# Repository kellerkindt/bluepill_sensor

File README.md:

# Bluepill Ethernet Sensor Extension Board

This project is about an extension board for the Bluepill (based on stm32f103) I develop in my spare time.
I use this board to monitor the temperature at various places in my house, the CO2 concentration at my desktop as well as my energy consumption.
All values are polled through the network (UDP) by munin. You can even watch some live readings [here](https://home.watzko.de).
The board is designed to be stacked on top of another expansion PCB and provides the following functionality itself:

 - an ethernet connection via W5500
 - an OneWire connector (3.3v, GND, Data)
 - an EEPROM socket (AT93C46W via DIP or SOIC)
 - temperature sensor (LM75 SOIC)
 - a (factory reset) button
 - 2x status LEDs
    - with jumpers to disconnect them from the RTC pins (PC14 & PC15)
 - 8x LEDs via on-board GPIO-I2C-Expander PCF8574 (SOIC)
 - I2C-2 connector for further frontend expansion (3.3v, GND, SDA and SCL)

 \
(Board rev 2 connected to ethernet and with an OneWire temperature sensor)

### Pinout

On the top and bottom borders the board provides the same pin-layout as the Bluepill itself.
The top row is directly connected to the Bluepill and no pin is used by the board.
Although all pins of the bottom row are used by components on the board, they are routed through nonetheless
(keep in mind that the 2x2 jumper pins can disconnect PC14 & PC15 from the board entirely - including from the bottom pins). 

## Gallery

### Animated assembly of board rev 3.1

### CO2 expansion

todo

### GPIO LED Demo

todo

#### License

<sup>
Licensed under either of <a href="LICENSE-APACHE">Apache License, Version
2.0</a> or <a href="LICENSE-MIT">MIT license</a> at your option.
</sup>

<br>

<sub>
Unless you explicitly state otherwise, any contribution intentionally submitted
for inclusion in this crate by you, as defined in the Apache-2.0 license, shall
be dual licensed as above, without any additional terms or conditions.
</sub>

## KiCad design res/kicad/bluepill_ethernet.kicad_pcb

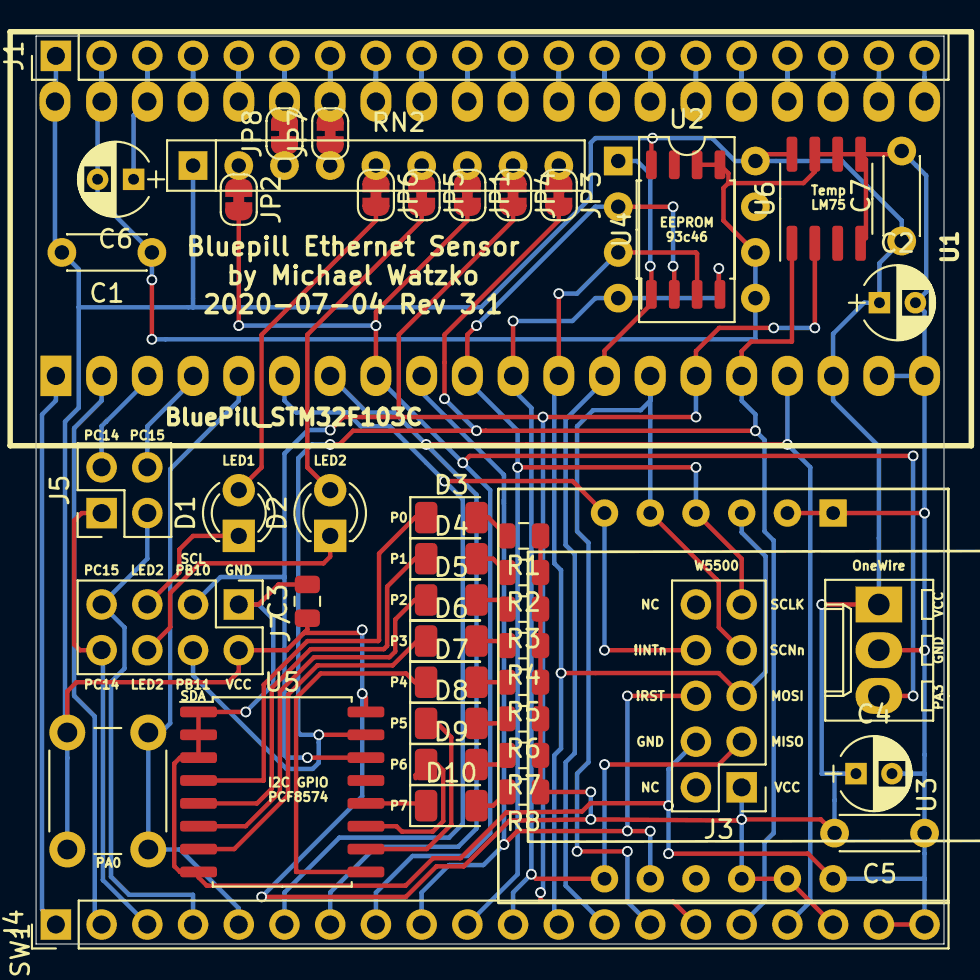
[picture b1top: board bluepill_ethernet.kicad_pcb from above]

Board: 2 copper layers, 50.4 x 50.4 mm, 47 parts (0 on the bottom side), 66 nets.

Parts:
C1, C5, C7: C; C_Disc_D4.3mm_W1.9mm_P5.00mm
C2, C4, C6: CP; CP_Radial_D4.0mm_P2.00mm
C3: C; C_0805_2012Metric
D1, D2: LED; LED_D3.0mm
D3, D4, D5, D6, D7, D8, D9, D10: LED; LED_1206_3216Metric
J1, J4: HEADER-1x20; Pin_Header_Straight_1x20_Pitch2.54mm
J2: Conn_01x03; Molex_KK-6410-03_03x2.54mm_Straight
J3: Conn_02x05_Odd_Even; Pin_Header_Straight_2x05_Pitch2.54mm
J5: Conn_02x02_Odd_Even; PinHeader_2x02_P2.54mm_Vertical
J7: Conn_02x04_Odd_Even; PinHeader_2x04_P2.54mm_Vertical
JP1, JP2, JP3, JP4, JP5, JP6, JP7, JP8: SolderJumper_2_Bridged; SolderJumper-2_P1.3mm_Bridged_RoundedPad1.0x1.5mm
R1, R2, R3, R4, R5, R6, R7, R8: R; R_0805_2012Metric
RN2: 4,7k; R_Array_SIP9
SW1: SW_Push; SW_PUSH_6mm
U1: BluePill_STM32F103C
U2: 93C46; DIP-8_W7.62mm
U3: WIZ850io
U4: 93C46; SOIC-8_5.23x5.23mm_P1.27mm
U5: PCF8574A; SOIC-16W_7.5x10.3mm_P1.27mm
U6: LM75B; SOIC-8_3.9x4.9mm_P1.27mm

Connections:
GND: C1.1, C2.2, C3.2, C4.2, C5.1, C6.2, C7.2, J1.2, J2.2, J3.4, J4.19, J4.20, J7.1, U1.19, U1.20, U1.39, U2.5, U2.6, U3.1, U3.2, U3.12, U4.5, U4.6, U5.1, U5.2, U5.3, U5.8, U6.4, U6.5, U6.6, U6.7
unnamed: C6.1, J1.3, U1.38
unnamed: D1.1, J7.5
unnamed: D2.1, J7.6
unnamed: D3.1, U5.4
unnamed: D3.2, R1.2
unnamed: D4.1, U5.5
unnamed: D4.2, R2.2
unnamed: D5.1, U5.6
unnamed: D5.2, R3.2
unnamed: D6.1, U5.7
unnamed: D6.2, R4.2
unnamed: D7.1, U5.9
unnamed: D7.2, R5.2
unnamed: D8.1, U5.10
unnamed: D8.2, R6.2
unnamed: D9.1, U5.11
unnamed: D9.2, R7.2
unnamed: D10.1, U5.12
unnamed: D10.2, R8.2
unnamed: J1.4, U1.37
unnamed: J1.5, U1.36
unnamed: J1.6, JP8.2, U1.35
unnamed: J1.7, JP7.2, U1.34
unnamed: J1.8, U1.33
unnamed: J1.9, U1.32
unnamed: J1.10, U1.31
unnamed: J1.11, U1.30
unnamed: J1.12, U1.29
unnamed: J1.13, U1.28
unnamed: J1.14, U1.27
unnamed: J1.15, U1.26
unnamed: J1.16, U1.25
unnamed: J1.17, U1.24
unnamed: J1.18, U1.23
unnamed: J1.19, U1.22
unnamed: J1.20, U1.21
unnamed: J2.3, J4.8, JP1.2, JP2.2, U1.8
unnamed: J3.3, J4.11, U1.11, U2.4, U3.7, U4.4
unnamed: J3.5, J4.12, U1.12, U2.3, U3.3, U4.3
unnamed: J3.6, J4.9, U1.9, U3.8
unnamed: J3.7, J4.14, U1.14, U3.5
unnamed: J3.8, J4.6, U1.6, U3.6
unnamed: J3.9, J4.10, U1.10, U2.2, U3.4, U4.2
unnamed: J4.1, U1.1
unnamed: J4.2, U1.2
unnamed: J4.3, J5.1, J7.8
unnamed: J4.4, J5.3, J7.7
unnamed: J4.5, SW1.2, U1.5
unnamed: J4.13, U1.13, U2.1, U4.1
unnamed: J4.7, J4.17, U1.7, U1.17
unnamed: J5.2, U1.3
unnamed: J5.4, U1.4
unnamed: JP1.1, RN2.7
unnamed: JP2.1, RN2.2
unnamed: JP3.1, RN2.9
unnamed: JP4.1, RN2.8
unnamed: JP5.1, RN2.6
unnamed: JP6.1, RN2.5
unnamed: JP7.1, RN2.4
unnamed: JP8.1, RN2.3
VCC: C1.2, C2.1, C3.1, C4.1, C5.2, C7.1, J1.1, J2.1, J3.1, J4.18, J7.2, R1.1, R2.1, R3.1, R4.1, R5.1, R6.1, R7.1, R8.1, RN2.1, SW1.1, U1.18, U1.40, U2.8, U3.10, U3.11, U4.8, U5.16, U6.8
dled1: D1.2, JP6.2
dled2: D2.2, JP5.2
i2c1c: J4.15, J7.3, JP4.2, U1.15, U5.14, U6.2
i2c1d: J4.16, J7.4, JP3.2, U1.16, U5.15, U6.1

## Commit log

2018-02-15 Flash + write! to stdout works via debug.sh + server.sh, LED blinking does not work
2018-02-16 LED blinks
2018-02-17 Manual OpenDrain mode on PC14
2018-02-17 Can read from OneWire?
2018-02-17 OneWire implementation through stm32f103xx_hal
2018-02-17 Clenaup + Update to latest OneWire implementation with patched stm32f103xx_hal (OpenDrain patch)
2018-02-18 Fix wrong compile target, does now find device via onewire
2018-02-18 Use latest DS18B20 implementation from the onewire crate
2018-03-09 Finally able to read mac
2018-03-10 Can transmit temperature via UDP packet
2018-03-11 Processing and answering very basic Request (sensor_common)
2018-03-11 Use NetworkEndian
2018-03-11 Overhaul for the udp handling
2018-03-11 Remove enc28j60 dependency
2018-03-17 Handling discover + read specified requests
2018-03-30 Update code for custom pcb (including eeprom + self reset)
2018-03-30 Remove display (loops so much faster now o.O)
2018-03-30 W5500 no longer consumes SPI
2018-03-31 Read configuration from eeprom
2018-03-31 Rename Configuration to NetworkConfiguration, implement RetrieveVersionInformation and RetrieveNetworkConfiguration
2018-03-31 Add SetNetworkIpSubnetGateway and SetNetworkMac handling
2018-04-01 Introduce Platform which hides internal HW configuration
2018-04-01 Cleanup cargo information
2018-04-01 Remove intellij module file
2018-04-01 Add draft kicad files
2018-04-01 Fix binary path
2018-04-01 Cleanup
2018-04-01 Current state does not respond, what is going on
2018-04-01 @last commit: It works, I am stupid
2018-04-24 Add revision information for kicad circuit (rev1)
2018-04-24 Add button to kicad circuit for 'factory reset' the configuration (delete eeprom)
2018-05-31 Revision 2.0
2018-06-05 Fix production issues (also add molex pin for other W5500 boards)
2018-06-08 Update to latest rust / stm32f103xx-hal changes
2018-06-10 Update to latest stm-crate changes + add RetrieveDeviceInformation
2018-06-10 Add Am2302 integration through custom read
2018-08-05 Include AM2302, fix it and use MonoTimer (to be replaced by CountDown-timer)
2018-08-08 Version 0.3.4: allow on right side on bluepill (below 3,3v/GND/5v + 2xI2C) to plug in up to 13 AM2302 sensors via custom read 0-12
2018-08-26 Version 0.3.6: Fix RetrieveDeviceInformation error causing operlap in returned values
2018-08-26 Preparations for second onewire bus
2018-09-01 Version 0.2.3: Add workaround for MonoTimer, add support for multiple OneWire busses, reduce Am2302 pins by two (keep CAN free)
2018-09-01 Dont fail to collect onewire values if one bus is erronous
2018-09-01 Version 0.3.9: 3s press on button causes NetworkConfiguration reset to default (all 3 leds turn on)
2018-09-02 Add padding byte in device information
2018-09-02 Reenable remote reset
2018-09-02 Remove kicad backup files
2018-09-02 Add kicad rescue files
2018-09-02 Include target in build command to be independen from .cargo/config
2018-09-02 Freaking tape versions together, dont u dare to change!
2018-09-02 Fix of compiler warnings
2018-09-02 Fix compiler warnings, dont use hack for DWT anymore, instead use patched MonoTimer, show udp error on yellow LED
2018-09-02 Add build.sh to only try to build the project
2018-09-02 rustfmt
2018-09-02 Add Platform::discover_onewire_devices, use that instead of legacy code
2018-09-02 Remove legacy function discover_all_on_one_wire
2018-09-02 Add Platform::onewire_prepare_read and Platform::onewire_read
2018-10-27 Remove old gen-examples.sh
2018-10-27 Add .gitlab-ci.yml for github mirroring
2018-10-27 Upgrade to build with rust 1.31/1.30
2018-10-27 Update repository url
2018-12-08 Remove direct dependency on stm32f103xx
2018-12-08 Get flashing work again
2018-12-10 Build on stable rust
2018-12-11 Use stm32f103 from git master
2019-02-03 Add new I2C bus support with write_read
2019-02-07 Update dependency versions
2019-02-12 Add basic uart communication, update to w5500 v0.2.0 (socket-refactor/state update)
2019-03-20 Can read CO2 sensor (requires actual power supply!)
2019-03-25 Hack together to get bmp280 'working' (kinda curios values)
2019-04-19 Add ADS1115
2019-04-21 Make read-custom 192 timeout after 500ms
2019-04-21 Move CO2 value to Palt struct
2019-04-22 Poll the Palt once a second for values
2019-04-23 Implement basic palt
2019-07-13 Whatever PALT related and not yet committed changes...
2019-08-01 Remvoe palt specific impl
2019-08-01 Update to make it compile with recent changes to W5500 again
2020-05-23 Update to edition 2018 and latest stm32f1xx-hal
2020-05-24 Fix uptime not increasing, 'async' freq measurement
2020-05-27 Simplify LTFM
2020-05-30 Start to cleanup, add infallible Input- and OutputPin-traits
2020-05-30 The great refactoring: make it more modular, throw out currently unused code
2020-05-30 Cleanup, re-add custom-read 251-254, fix unused time in LTFM::value
2020-05-31 Further cleanup
2020-05-31 Move the status led into System
2020-06-11 Check for open garage door
2020-06-16 board revision 3 alpha 1
2020-06-16 Ignore kicad backup files
2020-06-17 Board Rev 3.0
2020-06-22 Refactor to reduce complexity in main and prepare for modules
2020-06-22 Refactor to reduce main() as a single line + allow error dump retrieval
2020-06-22 Put ECC module behind (default) feature gate
2020-06-22 Do not set a default module and allow on flash.sh and build.sh to pass --features ecc for example
2020-06-22 Provide FeaturedModule in DeviceInformation and improve feature flagging
2020-06-22 Rename ElectricCounterModule to ElectricityMeter
2020-06-22 Version 0.4.0: Upgrade to rev 3.0 boards on default with fallback feature
2020-06-23 Version 0.4.1: Add IndependentWatchdog with 5s intervals and reset the network on error recovery
2020-06-24 Move watchdog from Platform to System
2020-06-24 Move kicad libraries into this repository
2020-06-26 Add pumping system module
2020-06-28 Add basic PumpingState
2020-06-28 Add custom-read 200-204 to read pump+error state and counter level
2020-06-29 Adjust thresholds
2020-06-30 Board rev 3.1: Fix invalid pcf8574 footprint (20->16 pins)
2020-07-01 Replace TSSOP packages with SOIC packages
2020-07-04 Move molex pins and w5500 into 2,54mm raster
2020-08-09 Version 0.4.2: Add PreFail and Failure states which stops pumping at all eventually
2020-08-09 Version 0.4.3: Allow multiple pre-fail passes with increased interval before failing eventually
2020-11-21 Fix lint intra_doc_link_resolution_failure
2020-11-21 Upgrade to stm32f1xx-hal 0.7.0
2021-03-23 Update to most recent w5500 version with the embedded_nal UDP traits
2021-03-23 Add env (currently only co2) module
2021-04-06 No longer default to a board-revision, require explicit feature flag
2021-04-06 Detect and re-init a crashed / re-bootet w5500 chip
2021-04-07 Update to w5500 operation without moving ownership
2021-04-15 Move SPI1 related components to their own struct / subsystem
2021-04-16 Fix imports
2021-04-17 Create subsystem i2c
2021-04-18 Add command line hint for china clones of stm32f103
2021-04-18 Add values for caps, resistotrs, ... for board rev 3.1
2021-04-20 Add SCL and SDA labels to the pin header
2021-04-20 Fix board-rev handling and imports
2021-04-20 Add SNTP support
2021-07-07 Implement ListComponents{,AndNames} and RetrieveProperty with minimalistic properties subset
2021-07-07 Add basic and WIP README with images and dirtypcbs zip
2021-07-07 Implement basic property querying for the env module
2021-07-07 Add properties to ElectricityMeter and dummy to nop + PumpingSystem
2021-07-11 Properly respond with PropertyReportV1 if requested
2021-07-11 Implementmore platform properties
2021-07-17 Fix visibility if subsystem_i2c
2022-03-13 Add pump state status string
2022-03-13 Add fifth pin to the LongTimeFreqMeasurement
2022-03-13 Fix range for fifth ltfm in em-module
2022-06-21 Add property accessors for PumpState module
2022-07-18 Remove RequestHandle body from PumpState
2022-07-18 Fix RetrieveProperty for longer paths
2022-07-26 Add solax module
2022-07-26 Cleanup and check address confirmation
2022-07-26 Add some notes regarding the constants
2022-07-30 On an invalid PropertyReportV1 deserialization break gracefully?
2022-07-30 Add QueryLive data interpretation and Property serving
2022-07-30 Cache LiveData for 1.25s
2022-07-30 Reduce max age for LiveData to 750msE
2022-08-07 Move solax data types to its own crate
2022-08-07 Add basic data types
2022-08-07 Move solax-modbus in as subtree
2022-08-07 Add f32 conversion methods
2022-08-07 Use solax-modbus f32 conversion methods
2022-09-07 Use ListComponentResponder and RetrievePropertyResponder from sensor_common
2022-09-11 Use property_read_fn! and property_write_fn! macros from sensor_common
2022-09-11 Cleanup solax module imports and downgrade to simple module file
